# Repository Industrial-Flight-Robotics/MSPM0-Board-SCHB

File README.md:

# MSPM0-Board-SCHB
A Texas Instruments Arm based Microcontroller Development Board using the MSPM0G3507SPTR

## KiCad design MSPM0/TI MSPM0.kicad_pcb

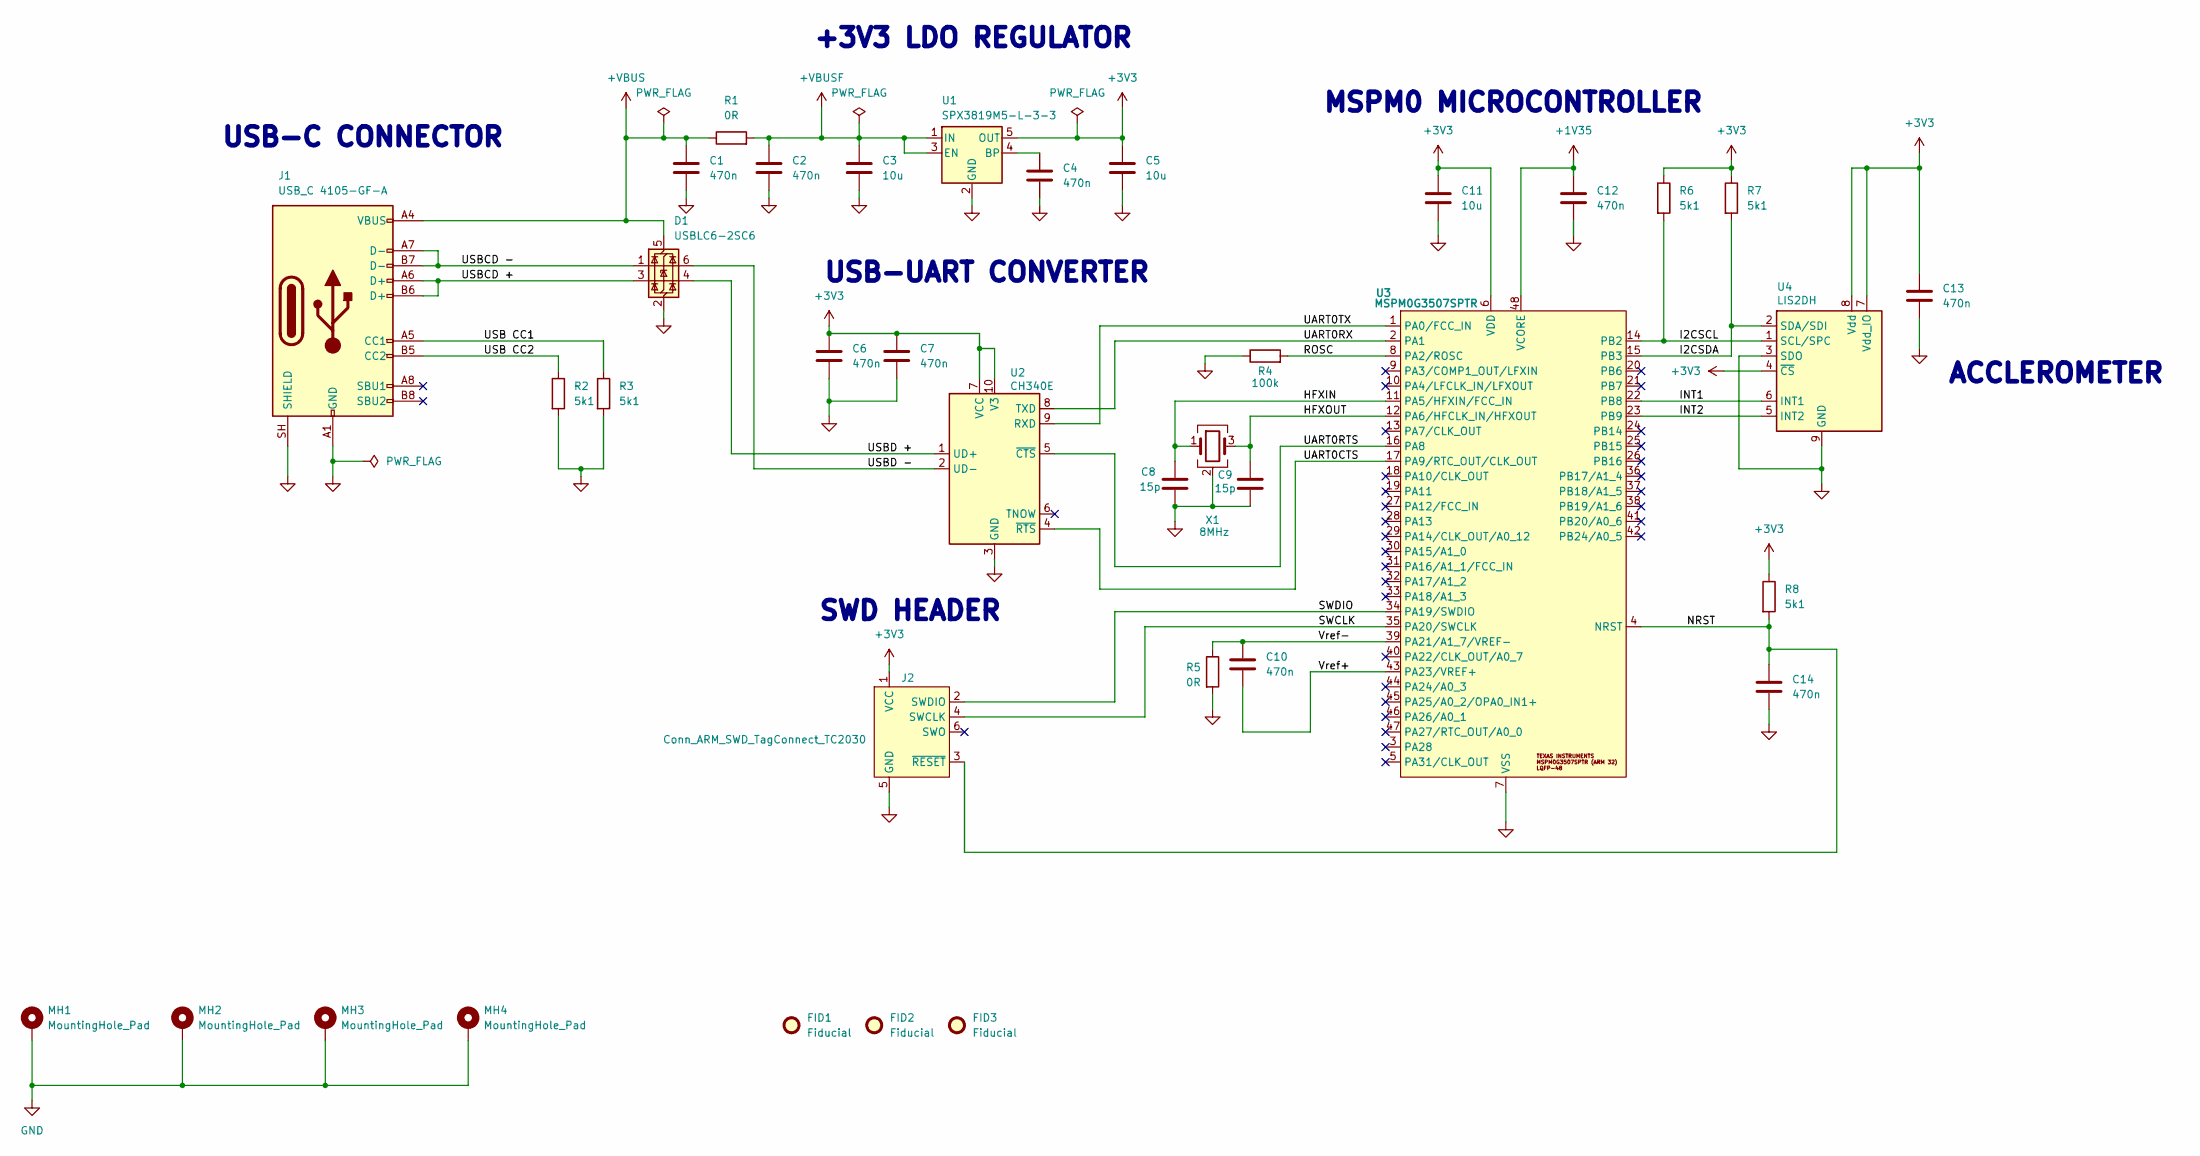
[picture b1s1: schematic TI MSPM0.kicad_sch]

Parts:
C1, C2, C4, C6, C7, C10, C12, C13, C14: 470n; C_0603_1608Metric
C3, C5, C11: 10u; C_0805_2012Metric; Manufacturer Part Number CL21A106KAYNNNE; LCSC C15850
C8, C9: 15p; C_0603_1608Metric
D1: USBLC6-2SC6; SOT-23-6
FID1, FID2, FID3: Fiducial; Fiducial_1mm_Mask2mm
J1: USB_C 4105-GF-A; USB_C_Receptacle_GCT_USB4105-xx-A_16P_TopMnt_Horizontal
J2: Conn_ARM_SWD_TagConnect_TC2030; Tag-Connect_TC2030-IDC-FP_2x03_P1.27mm_Vertical
MH1, MH2, MH3, MH4: MountingHole_Pad; MountingHole_3.2mm_M3_Pad_Via
R1, R5: 0R; R_0603_1608Metric
R2, R3, R6, R7, R8: 5k1; R_0603_1608Metric
R4: 100k; R_0603_1608Metric
U1: SPX3819M5-L-3-3; SOT-23-5
U2: CH340E; MSOP-10_3x3mm_P0.5mm
U3: MSPM0G3507SPTR; LQFP-48_7x7mm_P0.5mm; LCSC C22362630
U4: LIS2DH; LGA-14_2x2mm_P0.35mm_LayoutBorder3x4y
X1: 8MHz; Crystal_SMD_3225-4Pin_3.2x2.5mm

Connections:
+1V35: C12.1, U3.48 (VCORE)
+3V3: C5.1, C6.1, C7.1, C11.1, C13.1, J2.1 (VCC), R6.1, R7.1, R8.1, U1.5 (OUT), U2.7 (VCC), U2.10 (V3), U3.6 (VDD), U4.4 (~CS), U4.7 (Vdd_IO), U4.8 (Vdd)
+VBUS: C1.1, D1.5 (VBUS), J1.A4 (VBUS), J1.A9 (VBUS), J1.B4 (VBUS), J1.B9 (VBUS), R1.1
+VBUSF: C2.1, C3.1, R1.2, U1.1 (IN), U1.3 (EN)
/HFXIN: C8.1, U3.11 (PA5/HFXIN/FCC_IN), X1.1
/HFXOUT: C9.1, U3.12 (PA6/HFCLK_IN/HFXOUT), X1.3
/I2CSCL: R6.2, U3.14 (PB2), U4.1 (SCL/SPC)
/I2CSDA: R7.2, U3.15 (PB3), U4.2 (SDA/SDI)
/INT1: U3.22 (PB8), U4.6 (INT1)
/INT2: U3.23 (PB9), U4.5 (INT2)
/NRST: C14.1, J2.3 (~RESET), R8.2, U3.4 (NRST)
/ROSC: R4.2, U3.8 (PA2/ROSC)
/SWCLK: J2.4 (SWCLK), U3.35 (PA20/SWCLK)
/SWDIO: J2.2 (SWDIO), U3.34 (PA19/SWDIO)
/UART0CTS: U2.4 (~RTS), U3.17 (PA9/RTC_OUT/CLK_OUT)
/UART0RTS: U2.5 (~CTS), U3.16 (PA8)
/UART0RX: U2.8 (TXD), U3.2 (PA1)
/UART0TX: U2.9 (RXD), U3.1 (PA0/FCC_IN)
/USB CC1: J1.A5 (CC1), R3.1
/USB CC2: J1.B5 (CC2), R2.1
/USBCD +: D1.3 (I/O2), J1.A6 (D+), J1.B6 (D+)
/USBCD -: D1.1 (I/O1), J1.A7 (D-), J1.B7 (D-)
/USBD +: D1.4 (I/O2), U2.1 (UD+)
/USBD -: D1.6 (I/O1), U2.2 (UD-)
/Vref+: C10.2, U3.43 (PA23/VREF+)
/Vref-: C10.1, R5.1, U3.39 (PA21/A1_7/VREF-)
GND: C1.2, C2.2, C3.2, C4.2, C5.2, C6.2, C7.2, C8.2, C9.2, C11.2, C12.2, C13.2, C14.2, D1.2 (GND), J1.A1 (GND), J1.A12 (GND), J1.B1 (GND), J1.B12 (GND), J1.SH (SHIELD), J2.5 (GND), MH1.1 (1_1), MH2.1 (1_1), MH3.1 (1_1), MH4.1 (1_1), R2.2, R3.2, R4.1, R5.2, U1.2 (GND), U2.3 (GND), U3.7 (VSS), U4.3 (SDO), U4.9 (GND), U4.10 (GND), U4.11 (GND), U4.12 (GND), U4.13 (GND), U4.14 (GND), X1.2 (G), X1.4 (G)
unnamed: C4.1, U1.4 (BP)

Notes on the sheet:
USB-UART CONVERTER
ACCLEROMETER
USB-C CONNECTOR
MSPM0 MICROCONTROLLER
+3V3 LDO REGULATOR
SWD HEADER

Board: 2 copper layers, 37 parts (0 on the bottom side), 28 nets, no tracks yet.
